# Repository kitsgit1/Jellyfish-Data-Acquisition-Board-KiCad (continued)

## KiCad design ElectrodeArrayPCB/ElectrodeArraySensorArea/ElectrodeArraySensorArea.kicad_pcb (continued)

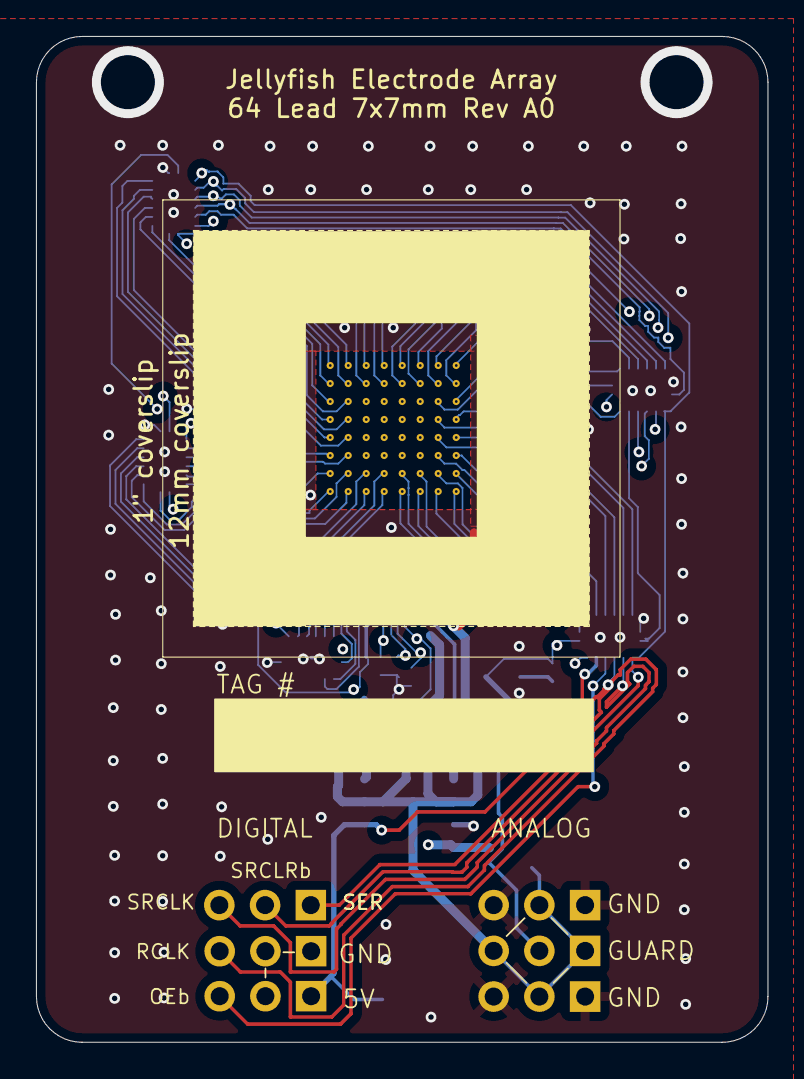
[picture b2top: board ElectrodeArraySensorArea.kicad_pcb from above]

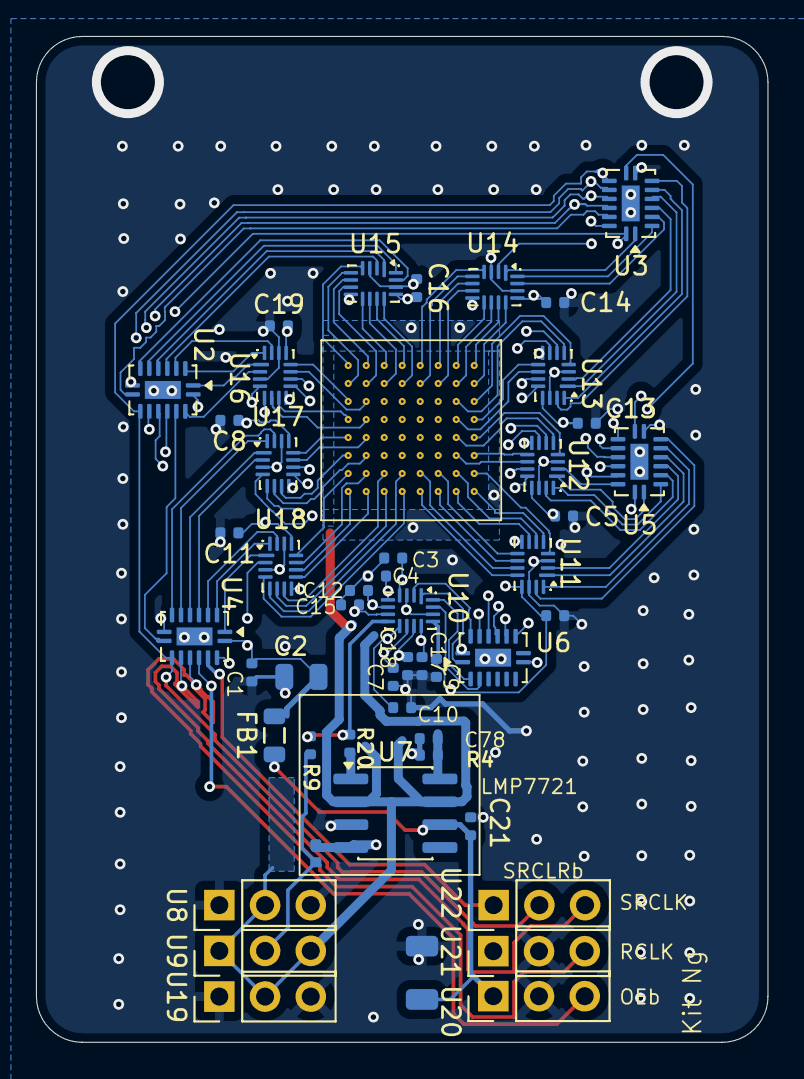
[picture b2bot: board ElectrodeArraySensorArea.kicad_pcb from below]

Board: 4 copper layers, 40.6 x 55.9 mm, 49 parts (48 on the bottom side), 126 nets.

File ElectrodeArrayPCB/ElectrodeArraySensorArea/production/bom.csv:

Designator,Footprint,Quantity,Value,LCSC Part #
"C1, C11, C13, C14, C16, C19, C21, C5, C6, C8, C9",C_0402,11,100nF,C307331
"C10, C12, C15, C17, C18, C3, C4, C7",C_0402,8,47pF,C1567
C2,C_0805,1,10uF,C15850
C20,C_1206,1,47uF,C96123
C78,C_0402,1,10pF,C32949
FB1,FB_0805,1,~,C1015
"R20, R31, R9",R_0402,3,0Ω,C17168
R4,R_0402,1,10kΩ,C25744
U1,Electrode_Array_64_Square,1,~,
"U10, U11, U12, U13, U14, U15, U16, U17, U18",UQFN-16_1.8x2.6mm_P0.4mm,9,TMUX1108RSVR,
"U19, U20, U21, U22, U8, U9",PinHeader_1x03_P2.54mm_Vertical,6,DS1023-1x3SF11,C7509516
"U2, U3, U4, U5, U6",DHVQFN-16-1EP_2.5x3.5mm_P0.5mm_EP1x2mm,5,SN74LV595ABQBR,C7083313
U7,SOIC-8_3.9x4.9mm_P1.27mm,1,LMP7721,

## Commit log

2025-12-10 Initial commit
    Add fabbed board files for KiCad.
2025-12-10 Create README.md for Jellyfish Data Acquisition Board
    Added initial documentation for the Jellyfish Data Acquisition Board project, including hardware details for the Electrode and Digitizer boards.
